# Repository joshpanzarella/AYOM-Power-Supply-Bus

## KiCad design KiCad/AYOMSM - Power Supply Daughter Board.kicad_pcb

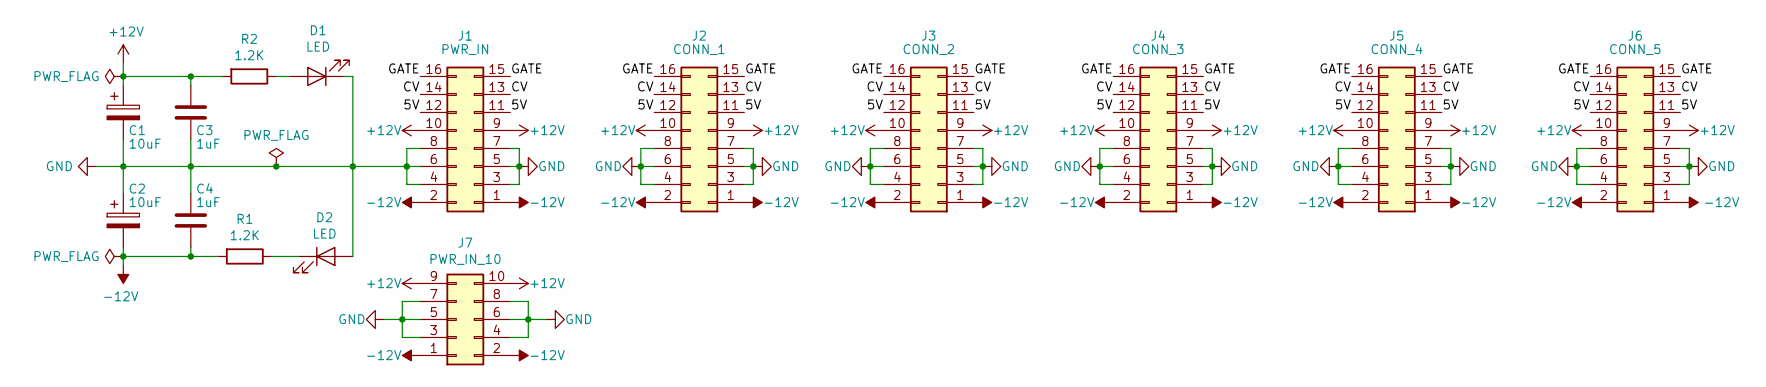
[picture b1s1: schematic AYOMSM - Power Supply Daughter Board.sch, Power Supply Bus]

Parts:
C1, C2: 10uF; C_Radial_D6.3mm_H11.0mm_P2.50mm
C3, C4: 1uF; C_Disc_D4.7mm_W2.5mm_P5.00mm
D1, D2: LED; LED_D3.0mm
J1: PWR_IN; IDC-Header_2x08_P2.54mm_Vertical
J2: CONN_1; IDC-Header_2x08_P2.54mm_Vertical
J3: CONN_2; IDC-Header_2x08_P2.54mm_Vertical
J4: CONN_3; IDC-Header_2x08_P2.54mm_Vertical
J5: CONN_4; IDC-Header_2x08_P2.54mm_Vertical
J6: CONN_5; IDC-Header_2x08_P2.54mm_Vertical
J7: PWR_IN_10; IDC-Header_2x05_P2.54mm_Vertical
R1, R2: 1.2K; R_Axial_DIN0207_L6.3mm_D2.5mm_P7.62mm_Horizontal

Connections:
+12V: C1.1, C3.1, J1.9, J1.10, J2.9, J2.10, J3.9, J3.10, J4.9, J4.10, J5.9, J5.10, J6.9, J6.10, J7.9, J7.10, R2.2
-12V: C2.2, C4.2, J1.1, J1.2, J2.1, J2.2, J3.1, J3.2, J4.1, J4.2, J5.1, J5.2, J6.1, J6.2, J7.1, J7.2, R1.2
/5V: J1.11, J1.12, J2.11, J2.12, J3.11, J3.12, J4.11, J4.12, J5.11, J5.12, J6.11, J6.12
/CV: J1.13, J1.14, J2.13, J2.14, J3.13, J3.14, J4.13, J4.14, J5.13, J5.14, J6.13, J6.14
/GATE: J1.15, J1.16, J2.15, J2.16, J3.15, J3.16, J4.15, J4.16, J5.15, J5.16, J6.15, J6.16
GND: C1.2, C2.1, C3.2, C4.1, D1.1 (K), D2.2 (A), J1.3, J1.4, J1.5, J1.6, J1.7, J1.8, J2.3, J2.4, J2.5, J2.6, J2.7, J2.8, J3.3, J3.4, J3.5, J3.6, J3.7, J3.8, J4.3, J4.4, J4.5, J4.6, J4.7, J4.8, J5.3, J5.4, J5.5, J5.6, J5.7, J5.8, J6.3, J6.4, J6.5, J6.6, J6.7, J6.8, J7.3, J7.4, J7.5, J7.6, J7.7, J7.8
unnamed: D1.2 (A), R2.1
unnamed: D2.1 (K), R1.1

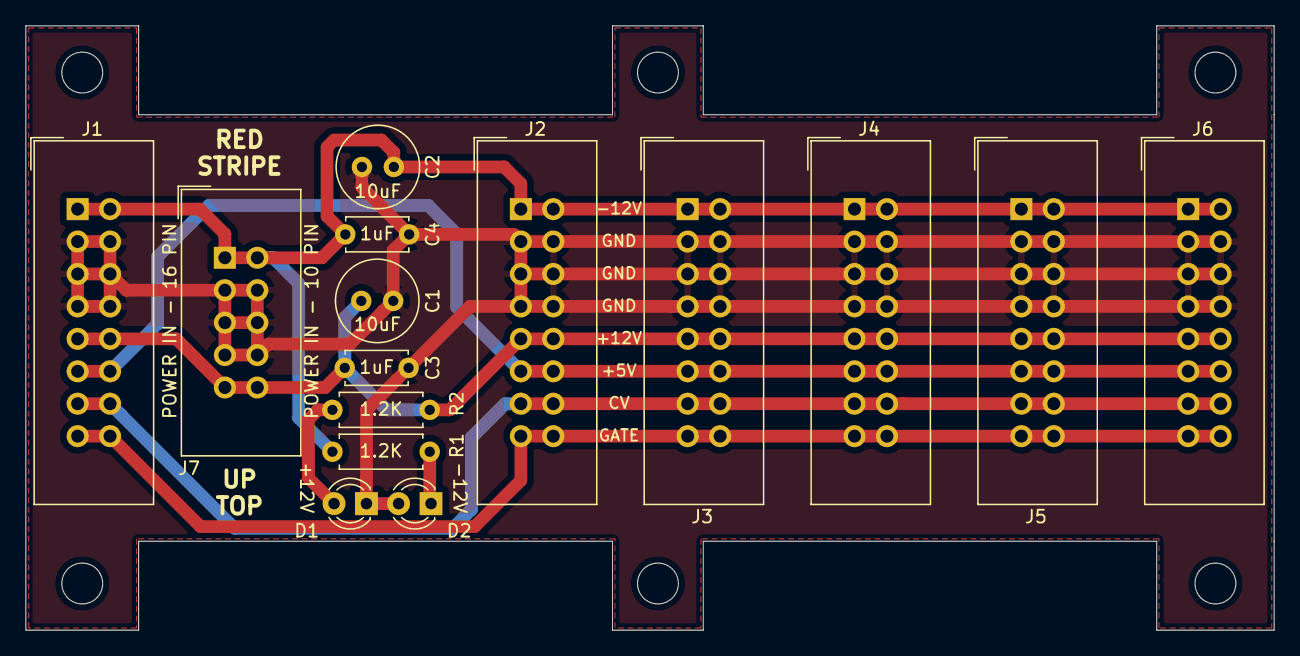
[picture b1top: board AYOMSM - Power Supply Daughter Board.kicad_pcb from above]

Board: 2 copper layers, 97.8 x 47.3 mm, 15 parts (0 on the bottom side), 8 nets.

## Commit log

2020-07-12 Added Gerbers and interactive BOM
2020-07-12 Added Gerbers archive
2020-07-20 Added 10-pin Power-In connector, updated layout
2020-07-20 Added new Gerbers and archive
2020-07-25 Updated BOM, ordering information, updated silkscreen, added README
2020-08-08 Updated silkscreen
2020-08-08 Added KiCad renders of PCB
2020-09-23 Changed name of Gerber archive
2020-09-23 Updated Gerber archive
2020-10-10 Updated Gerbers
2020-10-10 Updated acronyms
2020-10-10 Updated Gerber filenames
2020-10-13 Updated iBOM and netlist
2020-10-13 Updated iBOM name
2020-10-13 Updated Header and style changes
2020-10-13 Ibom style and header updates
2020-10-13 Updated header and styles
